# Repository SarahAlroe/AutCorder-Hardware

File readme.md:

Note: This is an early revision of the version 2 AutCorder hardware in testing. Works, but may not be ready for production. 

## Configuration jumpers 

- JP1 and JP2 provide options for enabling 3.3v on the last two pins of the FPC connector in either direction. This is for AF enabled OV5640 cameras. Untested, make sure pinout is correct. 

## Known issues 

- From V1 the replacement PDM microphone has tighter specifications, requiring a faster clock signal.

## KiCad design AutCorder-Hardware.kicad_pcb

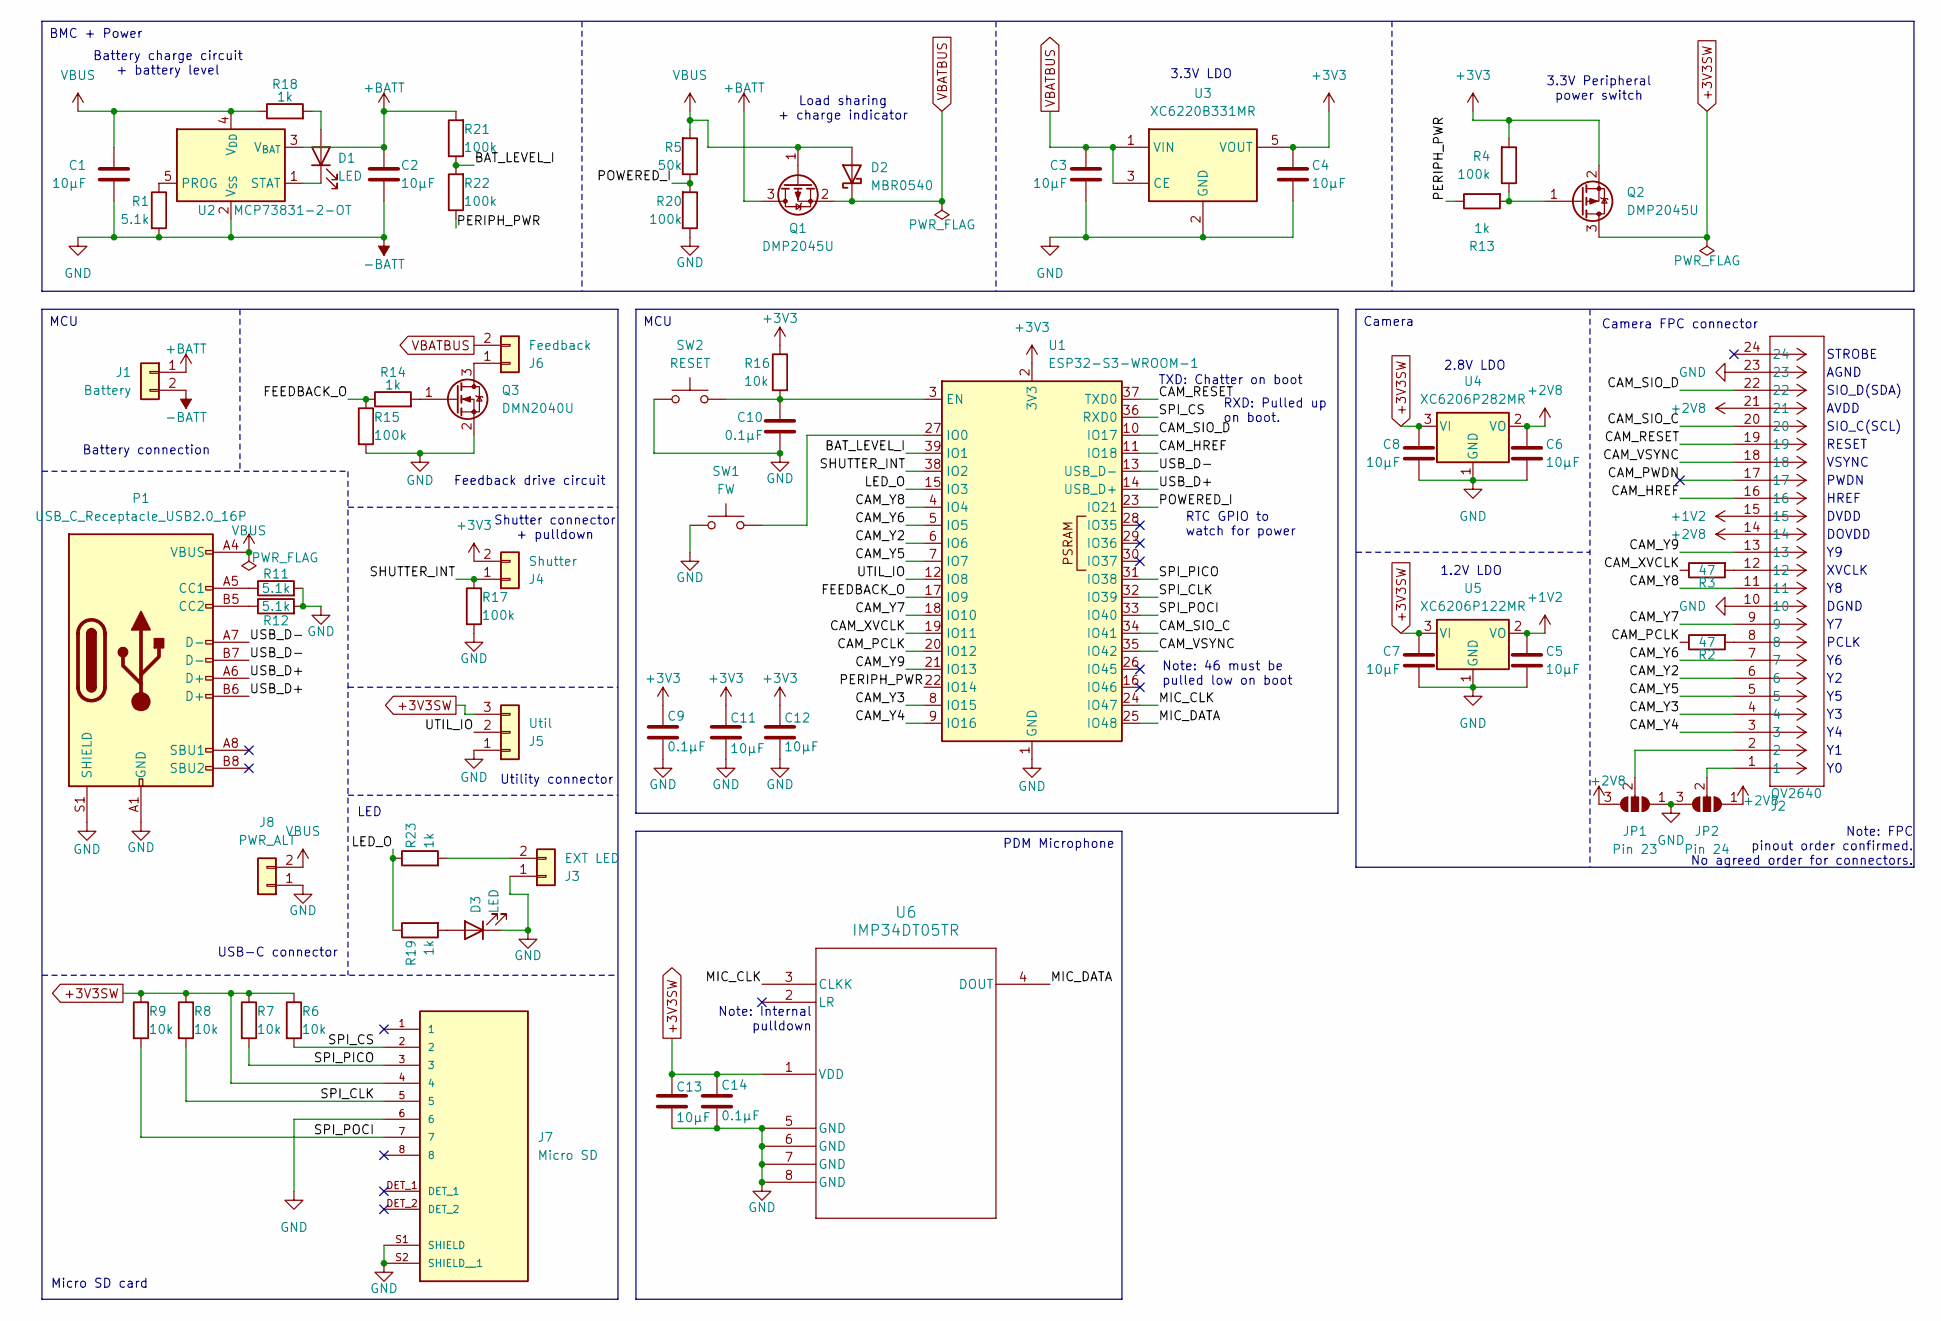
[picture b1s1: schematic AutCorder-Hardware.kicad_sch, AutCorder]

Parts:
C1, C2, C3, C4, C5, C6, C7, C8, C11, C12, C13: 10µF; C_0603_1608Metric
C9, C10, C14: 0.1µF; C_0603_1608Metric
D1, D3: LED; LED_0603_1608Metric
D2: MBR0540; D_SOD-123
J1: Battery; JST_PH_S2B-PH-K_1x02_P2.00mm_Horizontal
J2: OV2640; CONN_FFC2B35-24-x_GCT; PARTREV 1
J3: EXT LED; PinHeader_1x02_P2.00mm_Vertical
J4: Shutter; PinHeader_1x02_P2.00mm_Vertical
J5: Util; PinHeader_1x03_P2.00mm_Vertical
J6: Feedback; PinHeader_1x02_P2.00mm_Vertical
J7: Micro SD; AMPHENOL_10067099-200LF; PARTREV H
J8: PWR_ALT; PinHeader_1x02_P2.00mm_Vertical
JP1: Pin 23; SolderJumper-3_P0.75mm_Open_Pad0.5x1mm
JP2: Pin 24; SolderJumper-3_P0.75mm_Open_Pad0.5x1mm
P1: USB_C_Receptacle_USB2.0_16P; USB_C_Receptacle_GCT_USB4105-xx-A_16P_TopMnt_Horizontal
Q1, Q2: DMP2045U; SOT-23
Q3: DMN2040U; SOT-23
R1, R11, R12: 5.1k; R_0603_1608Metric
R2, R3: 47; R_0603_1608Metric
R4, R15, R17, R20, R21, R22: 100k; R_0603_1608Metric
R5: 50k; R_0603_1608Metric
R6, R7, R8, R9, R16: 10k; R_0603_1608Metric
R13, R14, R18, R19, R23: 1k; R_0603_1608Metric
SW1: FW; SW_EVP-AWED4A
SW2: RESET; SW_EVP-AWED4A
U1: ESP32-S3-WROOM-1
U2: MCP73831-2-OT; SOT-23-5
U3: XC6220B331MR; SOT-23-5
U4: XC6206P282MR; SOT-23-3
U5: XC6206P122MR; SOT-23-3
U6: IMP34DT05TR; HCLGA_3X4X1_STM

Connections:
+1V2: C5.1, J2.15, U5.2 (VO)
+2V8: C6.1, J2.14, J2.21, JP1.3 (B), JP2.1 (A), U4.2 (VO)
+3V3: C4.1, C9.1, C11.1, C12.1, J4.2, Q2.2 (S), R4.2, R16.1, U1.2 (3V3), U3.5 (VOUT)
+3V3SW: C7.1, C8.1, C13.1, C14.1, J5.3, J7.4, Q2.3 (D), R6.1, R7.1, R8.1, R9.1, U4.3 (VI), U5.3 (VI), U6.1 (VDD)
+BATT: C2.1, J1.1, Q1.3 (D), R21.2, U2.3 (V_{BAT})
-BATT: C1.2, C2.2, C3.2, C4.2, C5.2, C6.2, C7.2, C8.2, C9.2, C10.2, C11.2, C12.2, C13.2, C14.2, D3.1 (K), J1.2, J2.10, J2.23, J3.1, J5.1, J7.6, J7.S1 (SHIELD), J7.S2 (SHIELD__1), J8.1, JP1.1 (A), JP2.3 (B), P1.A1 (GND), P1.A12 (GND), P1.B1 (GND), P1.B12 (GND), P1.S1 (SHIELD), Q3.2 (S), R1.2, R11.2, R12.2, R15.2, R17.2, R20.1, SW1.1, SW2.1, U1.1 (GND), U1.40 (GND), U1.41 (GND), U2.2 (V_{SS}), U3.2 (GND), U4.1 (GND), U5.1 (GND), U6.5 (GND), U6.6 (GND), U6.7 (GND), U6.8 (GND)
/BAT_LEVEL_I: R21.1, R22.2, U1.39 (IO1)
/CAM_HREF: J2.16, U1.11 (IO18)
/CAM_PCLK: R2.1, U1.20 (IO12)
/CAM_PWDN: J2.17
/CAM_RESET: J2.19, U1.37 (TXD0)
/CAM_SIO_C: J2.20, U1.34 (IO41)
/CAM_SIO_D: J2.22, U1.10 (IO17)
/CAM_VSYNC: J2.18, U1.35 (IO42)
/CAM_XVCLK: R3.1, U1.19 (IO11)
/CAM_Y2: J2.6, U1.6 (IO6)
/CAM_Y3: J2.4, U1.8 (IO15)
/CAM_Y4: J2.3, U1.9 (IO16)
/CAM_Y5: J2.5, U1.7 (IO7)
/CAM_Y6: J2.7, U1.5 (IO5)
/CAM_Y7: J2.9, U1.18 (IO10)
/CAM_Y8: J2.11, U1.4 (IO4)
/CAM_Y9: J2.13, U1.21 (IO13)
/FEEDBACK_O: R14.1, R15.1, U1.17 (IO9)
/LED_O: R19.1, R23.1, U1.15 (IO3)
/MIC_CLK: U1.24 (IO47), U6.3 (CLKK)
/MIC_DATA: U1.25 (IO48), U6.4 (DOUT)
/PERIPH_PWR: R13.1, R22.1, U1.22 (IO14)
/POWERED_I: R5.1, R20.2, U1.23 (IO21)
/SHUTTER_INT: J4.1, R17.1, U1.38 (IO2)
/SPI_CLK: J7.5, R8.2, U1.32 (IO39)
/SPI_CS: J7.2, R6.2, U1.36 (RXD0)
/SPI_PICO: J7.3, R7.2, U1.31 (IO38)
/SPI_POCI: J7.7, R9.2, U1.33 (IO40)
/USB_D+: P1.A6 (D+), P1.B6 (D+), U1.14 (USB_D+)
/USB_D-: P1.A7 (D-), P1.B7 (D-), U1.13 (USB_D-)
/UTIL_IO: J5.2, U1.12 (IO8)
unnamed: D1.2 (A), R18.2
unnamed: D1.1 (K), U2.1 (STAT)
unnamed: D3.2 (A), R19.2
unnamed: J2.8, R2.2
unnamed: J2.12, R3.2
unnamed: J3.2, R23.2
unnamed: J6.1, Q3.3 (D)
unnamed: J2.2, JP1.2 (C)
unnamed: J2.1, JP2.2 (C)
unnamed: P1.A5 (CC1), R11.1
unnamed: P1.B5 (CC2), R12.1
unnamed: Q2.1 (G), R4.1, R13.2
unnamed: Q3.1 (G), R14.2
unnamed: C10.1, R16.2, SW2.2, U1.3 (EN)
unnamed: SW1.2, U1.27 (IO0)
unnamed: R1.1, U2.5 (PROG)
VBATBUS: C3.1, D2.1 (K), J6.2, Q1.2 (S), U3.1 (VIN), U3.3 (CE)
VBUS: C1.1, D2.2 (A), J8.2, P1.A4 (VBUS), P1.A9 (VBUS), P1.B4 (VBUS), P1.B9 (VBUS), Q1.1 (G), R5.2, R18.1, U2.4 (V_{DD})

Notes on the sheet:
Micro SD card
Shutter connector + pulldown
Utility connector
Note: FPC pinout order confirmed. No agreed order for connectors.
RXD: Pulled up on boot.
SIO_D(SDA)
VSYNC
Note: Internal pulldown
Load sharing + charge indicator
1.2V LDO
TXD: Chatter on boot
DVDD
3.3V Peripheral power switch
HREF
RTC GPIO to watch for power
Note: 46 must be pulled low on boot
LED
AGND
3.3V LDO
STROBE
USB-C connector
2.8V LDO
Feedback drive circuit
DOVDD
DGND
RESET
PCLK
Battery charge circuit + battery level
PWDN
Battery connection
XVCLK
SIO_C(SCL)
Camera FPC connector
AVDD
PDM Microphone
MCU
Camera
BMC + Power

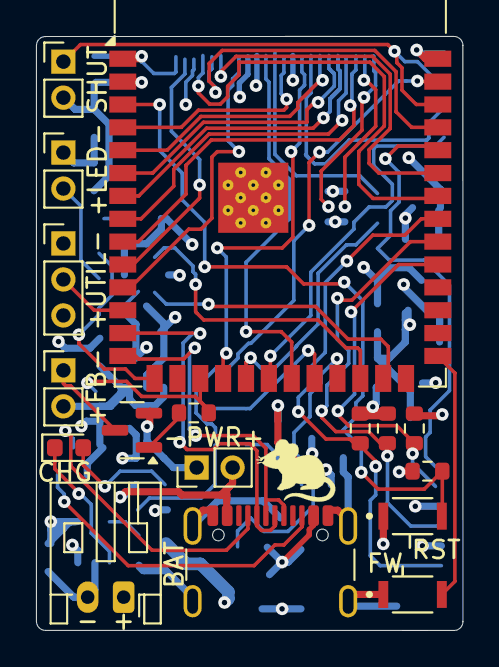
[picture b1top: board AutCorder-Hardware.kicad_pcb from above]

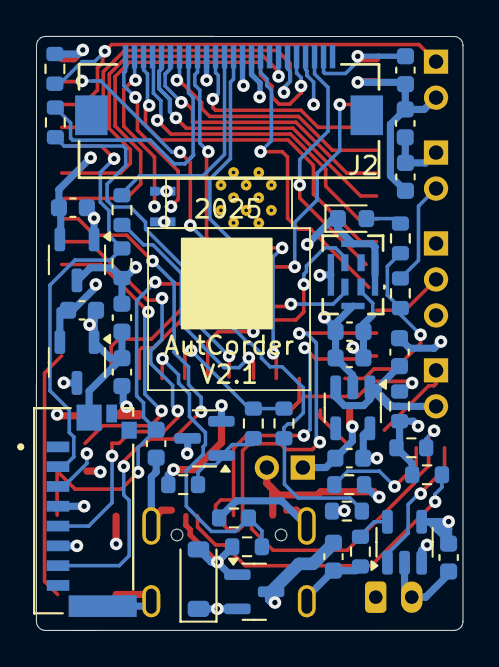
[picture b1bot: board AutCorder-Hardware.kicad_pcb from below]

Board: 4 copper layers, 23.7 x 33.0 mm, 61 parts (44 on the bottom side), 54 nets.

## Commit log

2024-09-23 Init
2024-09-23 Added gitignore
2024-11-05 V. 2.0
2024-11-05 Added readme
2024-11-05 V2 Minor changes
2025-01-08 Switched R5, Fixed USB data, Removed J3, Removed R10, Reoriented J1, Rearranged components.
2025-06-09 Switched to slimmer FPC connector. Rerouted.
2025-08-20 Added interactive BOM. Updated KiCad.
